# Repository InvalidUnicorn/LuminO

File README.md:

# LuminO
Winter Projekt des Moduls *Soft Skills und technische Kompetenz* der Carl von Ossietzky Universität Oldenburg.

## 3D Druck Dateien
Es stehen 2 verschiedene Versionen des Gehäuses zur Verfügung.
Eine 30mm und eine 50mm Version. Je nachdem welchen Außendurchmesser der LED Ring hat, muss die ensprechende Datei gedruckt werden.
Die Version für den kleineren Ring ist generell schneller und günstiger druckbar.

## Bauanleitung und Materialliste
Bauanleitung enthält eine bebilderte Schritt-für-Schritt Anleitung für den Zusammenbau des LuminOs.

Um das Projekt umzusetzen müssen einige Materialien besorgt werden.
Das Projekt kann mit oder ohne Akku umgesetzt werden. Entsprechende Teile sind optional.

| Komponente                   | Menge         |
| ---------------------------  | ------------- |
| D1 Mini Battery Shield       | 1x (optional) |
| 400mAh Lipo Akku             | 1x (optional) |
| Wemos D1 Mini                | 1x            |
| Mini Momentan Druckknopf     | 2x            |
| 12 LED Neopixel Ring         | 1x            |
| Lochrasterplatine (50x26 mm) | 1x            |

Die genaue Kapazität des Akkus ist zweitrangig. Er sollte nur nicht viel größer als 30x30 mm sein um in das Gehäuse zu passen.

## Testprogramm
LuminO_TEST enthält einen Arduino Sketch der nach dem Fertigstellen des Projekts auf den D1 Mini geladen werden kann.
Mit hilfe des Sketches können beide Buttons sowie der Led Ring auf richtige funktion geprüft werden.

## Lizenz
Die in diesem Repository enthaltenen Workshopmaterialien werden unter  zur Verfügung gestellt.

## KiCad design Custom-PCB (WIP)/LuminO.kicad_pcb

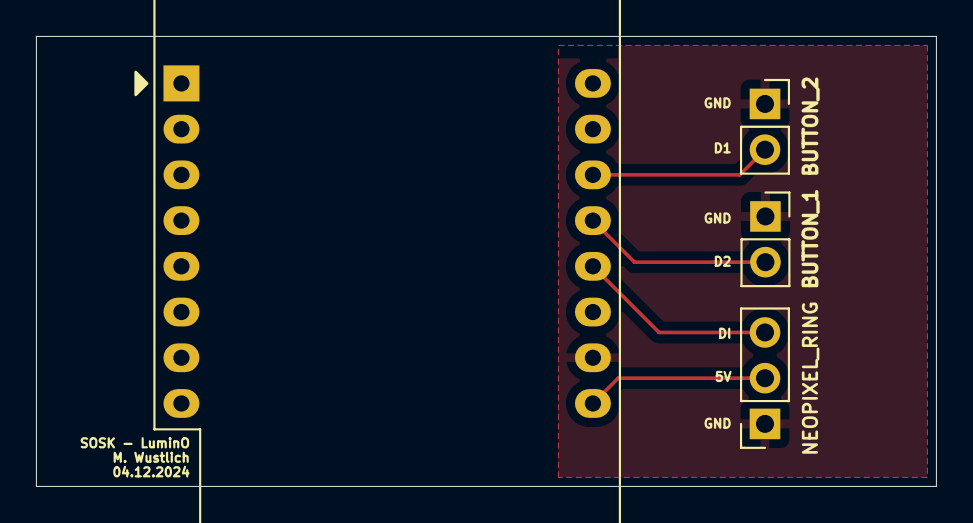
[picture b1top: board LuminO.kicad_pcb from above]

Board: 2 copper layers, 50.0 x 25.0 mm, 4 parts (0 on the bottom side), 5 nets.

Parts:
BUTTON_1, BUTTON_2: Conn_01x02_Socket; PinSocket_1x02_P2.54mm_Vertical
NEOPIXEL_RING: Conn_01x03_Socket; PinSocket_1x03_P2.54mm_Vertical
U1: WEMOS_D1_mini; WEMOS_D1_mini_light

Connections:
GND: BUTTON_1.1, BUTTON_2.1, NEOPIXEL_RING.1, U1.10 (GND)
unnamed: NEOPIXEL_RING.2, U1.9 (5V)
unnamed: NEOPIXEL_RING.3, U1.12 (D3)
unnamed: BUTTON_2.2, U1.14 (SCL/D1)
unnamed: BUTTON_1.2, U1.13 (SDA/D2)

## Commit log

2024-01-22 initial file upload
    2 versions of 3D models.
    Print them depending on your LED ring size.
2024-09-03 Update LICENSE
2024-09-03 Add License
2024-09-03 Rename LICENSE-CC-BY-NC-SA-4.0.md to LICENSE.md
2024-12-04 Updated Readme and added Aufbauanleitung
2025-10-15 Added Files for Custom PCB
    Added all Files of KI-CAD Project
2025-10-15 Rename READ.txt to README.txt
2025-10-16 example picture added
2025-11-19 Added Fusion 360 Project
2025-11-30 Create Directory
2025-11-30 Updated instructions
2025-11-30 Fixed Typo
2025-11-30 Rechtschreibung und Imperativ korrigiert
2025-11-30 Tabelle korrigiert und ˜*.docx-Beabeitungssperre entfernt
2025-11-30 MS Office Speerdateien zu .gitignore hinzugefügt
2025-12-01 Hinzufügen von neuen Höhen
    Hinzufügen von neuen Größen für die 30 mm Option, damit die neuen Akkus in das Gehäuse passen.
2025-12-01 Update Anleitung
    In der Materialliste steht jetzt das die Leisten in der Packung vom Wemos sind.
